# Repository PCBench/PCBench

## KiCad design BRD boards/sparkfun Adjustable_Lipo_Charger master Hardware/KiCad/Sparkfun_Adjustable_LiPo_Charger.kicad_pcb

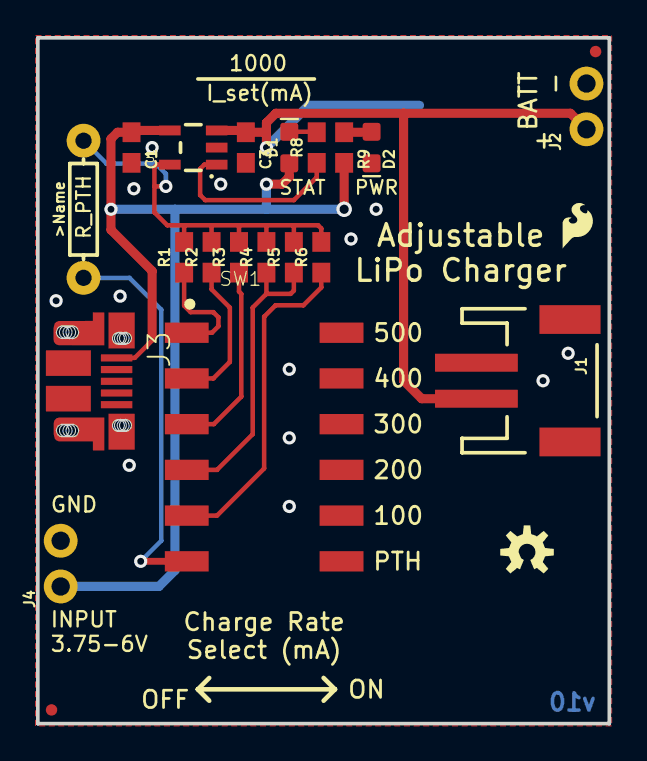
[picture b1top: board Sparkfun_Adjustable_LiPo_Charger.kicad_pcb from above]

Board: 2 copper layers, 31.8 x 38.1 mm, 28 parts (0 on the bottom side), 14 nets.

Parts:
BT1: BATTERY-24.5MM_SMD; BATTCON_24.5MM_SMD
C1, C3: 4.7uF; 0603
D1: BLUE; LED-0603
D2: RED; LED-0603
FD1, FD2, FD3, FD4: FIDUCIALUFIDUCIAL; FIDUCIAL-MICRO
FRAME1: FRAME-LETTER; CREATIVE_COMMONS
J1: JST_2MM_MALE; JST-2-SMD
J2, J4: CONN_021X02_NO_SILK; 1X02_NO_SILK
J3: USB_MICRO-B_HALF_PTH; USB-MICROB-PTH
LOGO1: SFE_LOGO_FLAME.1_INCH; SFE_LOGO_FLAME_.1
LOGO2: OSHW-LOGOS; OSHW-LOGO-S
R1: 2.0k; 0603
R2: 2.49k; 0603
R3: 3.3k; 0603
R4, R5, R6: 10k; 0603
R7: PTH; AXIAL-0.3
R8: 330; 0603
R9: 470; 0603
SW1: DIP-06; DIPSWITCH-06-SMD
U1: MCP73831; SOT23-5
U$1: SFE_LOGO_NAME_FLAME_.1

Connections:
/PROG: R1.2, R2.2, R3.2, R4.2, R5.2, R6.2, R7.P$2, U1.5
GND: BT1.2, C1.2, C3.2, D2.C, J1.1, J2.2, J3.GND, J4.2, SW1.7, SW1.8, SW1.9, SW1.10, SW1.11, SW1.12, U1.2
unnamed: D1.C, R8.2
unnamed: D2.A, R9.1
unnamed: J3.P$1, J3.P$2, J3.P$3, J3.P$4, J3.P$6, J3.P$8, J3.P$10, J3.P$12, J3.SHEILD2, J3.SHIELD, J3.SHIELD3, J3.SHIELD4
unnamed: R1.1, SW1.1
unnamed: R2.1, SW1.2
unnamed: R3.1, SW1.3
unnamed: R4.1, R5.1, SW1.4
unnamed: R6.1, SW1.5
unnamed: R7.P$1, SW1.6
unnamed: R8.1, U1.1
VCC: C1.1, D1.A, J3.VBUS, J4.1, R9.2, U1.4
V_BATT: BT1.3, C3.1, J1.2, J2.1, U1.3

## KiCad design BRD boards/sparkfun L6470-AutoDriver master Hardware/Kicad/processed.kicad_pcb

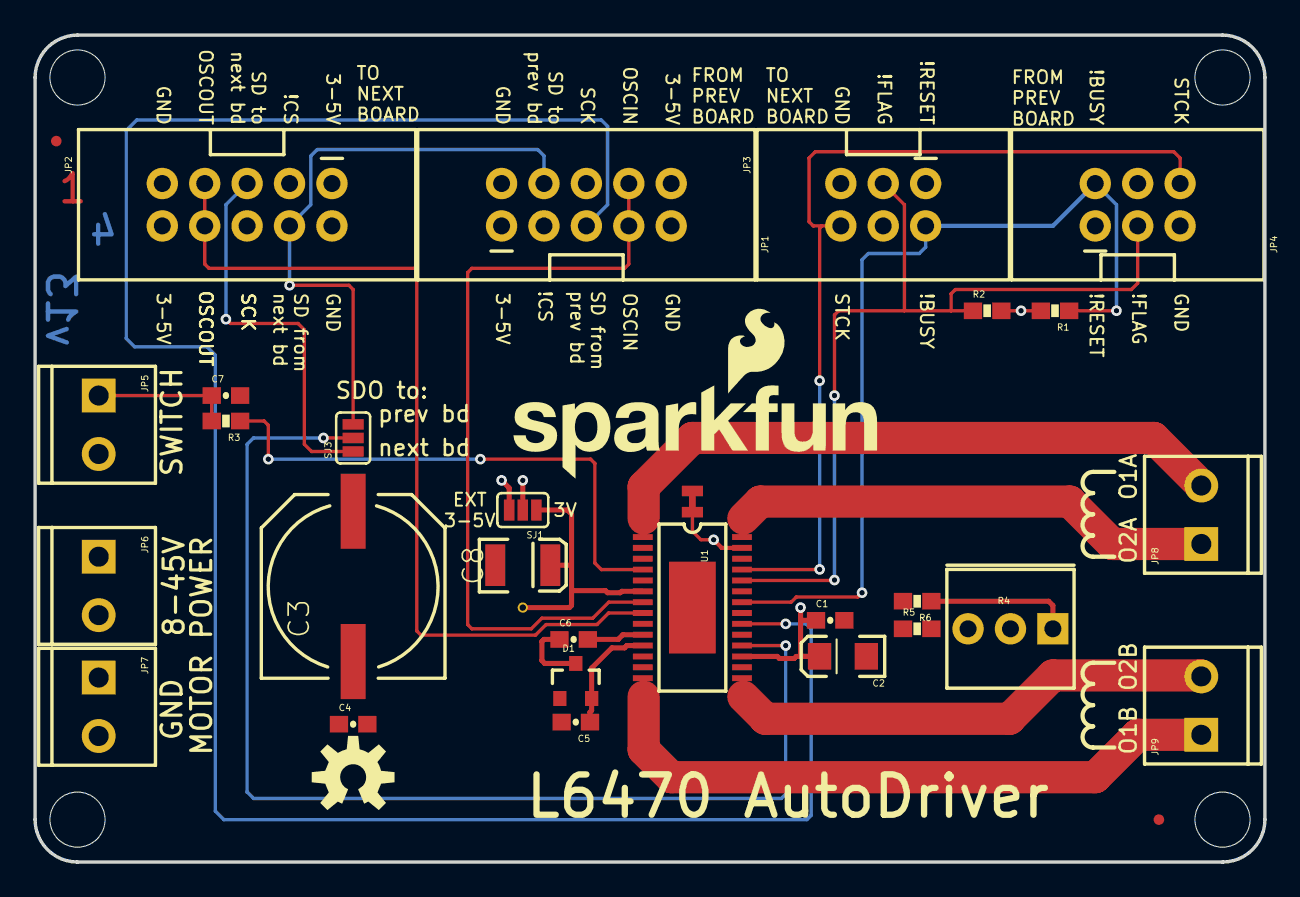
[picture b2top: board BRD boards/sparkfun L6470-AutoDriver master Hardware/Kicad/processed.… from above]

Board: 4 copper layers, 73.7 x 49.5 mm, 39 parts (0 on the bottom side), 23 nets.

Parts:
C1: 0.1uF; 0603-CAP
C2: 10uF; EIA3216
C3: 100uF; NIC_10X10.5_CAP
C4, C5: 0.22uF; 0603-CAP
C6, C7: 10nF; 0603-CAP
C8: 47uF; EIA3528
D1: BAV99; SOT23-3
FID1, FID2: FIDUCIALUFIDUCIAL; MICRO-FIDUCIAL
FRAME1: FRAME-LETTER; CREATIVE_COMMONS
JP1, JP2: M05X2SHD; 2X5-SHROUDED
JP3, JP4: M03X2SHROUD; 2X3-SHROUDED
JP5, JP6, JP7, JP8, JP9: M023.5MM; SCREWTERMINAL-3.5MM-2
LOGO1: OSHW-LOGOM; OSHW-LOGO-M
LOGO2: SFE_LOGO_NAME_FLAME.2_INCH; SFE_LOGO_NAME_FLAME_.2
R1, R2: 10k; 0603-RES
R3: 100; 0603-RES
R4: 200k; 3362U
R5: 8.2k; 0603-RES
R6: 33k; 0603-RES
SJ1, SJ3: JUMPER-PAD-3-2OF3_NC_BY_PASTE; PAD-JUMPER-3-2OF3_NC_BY_PASTE_YES_SILK_FULL_BOX
SJ2: 2PT_GND_TIE
STANDOFF1, STANDOFF2, STANDOFF3, STANDOFF4: STAND-OFF
TP1: TEST-POINTTP_15TH_THRU; TP_15TH
U1: L6470; HTSSOP28
U$4: FOUR_LAYER_WARNING

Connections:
3.3V: C8.A, SJ1.1, TP1.P$1, U1.6
5V: JP1.1, JP1.10, JP2.1, JP2.10, SJ1.3
/BUSYN: JP3.2, JP4.2, R1.1, U1.22
/D_RETURN: JP1.4, JP2.4, SJ3.3
/FLAGN: JP3.3, JP4.3, R2.1, U1.24
/OSCIN: JP1.7, JP1.8, U1.7
/OSCOUT: JP2.7, JP2.8, U1.8
/OUT1A: JP8.2, U1.1
/OUT1B: JP9.1, U1.14
/OUT2A: JP8.1, U1.28
/OUT2B: JP9.2, U1.15
/PGND: SJ2.P$2, U1.27
/SDI: JP1.5, U1.20
/SDO: SJ3.2, U1.18
/SDO_DOWNSTREAM: JP2.5, SJ3.1
/STCK: JP3.6, JP4.6, U1.25
/VLOGIC: C1.1, C2.A, R1.2, R2.2, SJ1.2, U1.17
unnamed: C5.1, D1.2, U1.11
unnamed: C6.1, D1.3
unnamed: C6.2, U1.10
unnamed: C7.1, JP5.1, R3.2
unnamed: R3.1, U1.4
unnamed: R4.P$1, R6.1

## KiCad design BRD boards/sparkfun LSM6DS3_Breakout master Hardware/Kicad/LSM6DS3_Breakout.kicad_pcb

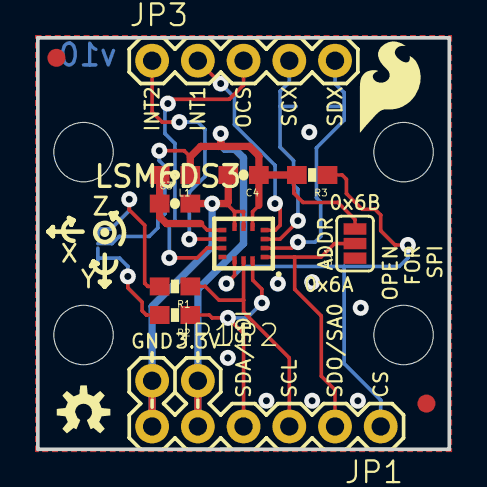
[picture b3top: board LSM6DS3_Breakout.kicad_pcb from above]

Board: 2 copper layers, 22.9 x 22.9 mm, 25 parts (0 on the bottom side), 14 nets.

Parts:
C3, C4: 0.1uF; 0603-CAP
FID1, FID2: FIDUCIAL1X2; FIDUCIAL-1X2
FRAME1: CREATIVE_COMMONS
JP1: IO; 1X06_NO_SILK_YES_STOP
JP2: 3.3V; 1X01_NO_SILK
JP3: IO; 1X05
JP11: GND; 1X01_NO_SILK
L1: RES-07859; 0603
LOGO1: SFE_LOGO_FLAME.2_INCH; SFE_LOGO_FLAME_.2
LOGO2: OSHW-LOGOS; OSHW-LOGO-S
LOGO3: SFE_LOGO_NAME_FLAME.1_INCH; SFE_LOGO_NAME_FLAME_.1
R1, R2: 4.7K; 0603-RES
R3: 10K; 0603-RES
SJ1: PAD-JUMPER-3-2OF3_NC_BY_PASTE_YES_SILK_FULL_BOX
SJ2: S_MODE; PAD-JUMPER-3-3OF3_NC_BY_TRACE_YES_SILK_FULL_BOX
SJ3, SJ4: JUMPER-PAD-2-NC_BY_TRACE; PAD-JUMPER-2-NC_BY_TRACE_YES_SILK
STANDOFF1, STANDOFF2, STANDOFF3, STANDOFF4: STAND-OFF
U2: LSM6DS3; LGA14L_DOT_INDICATOR

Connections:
3.3V: C4.1, JP1.5, JP2.1, L1.1, R3.2, SJ1.3, SJ2.2, U2.5
CS: JP1.1, R3.1, U2.12
GND: C3.2, C4.2, JP1.6, JP11.1, SJ1.1, SJ3.1, SJ4.1, U2.6, U2.7
INT1: JP3.2, U2.4
INT2: JP3.1, U2.9
unnamed: R1.2, SJ2.1
unnamed: R2.2, SJ2.3
OCS: JP3.3, U2.10
SCL: JP1.3, R1.1, U2.13
SCX: JP3.4, SJ4.2, U2.3
SDA: JP1.4, R2.1, U2.14
SDO/SA0: JP1.2, SJ1.2, U2.1
SDX: JP3.5, SJ3.2, U2.2
VDD: C3.1, L1.2, U2.8

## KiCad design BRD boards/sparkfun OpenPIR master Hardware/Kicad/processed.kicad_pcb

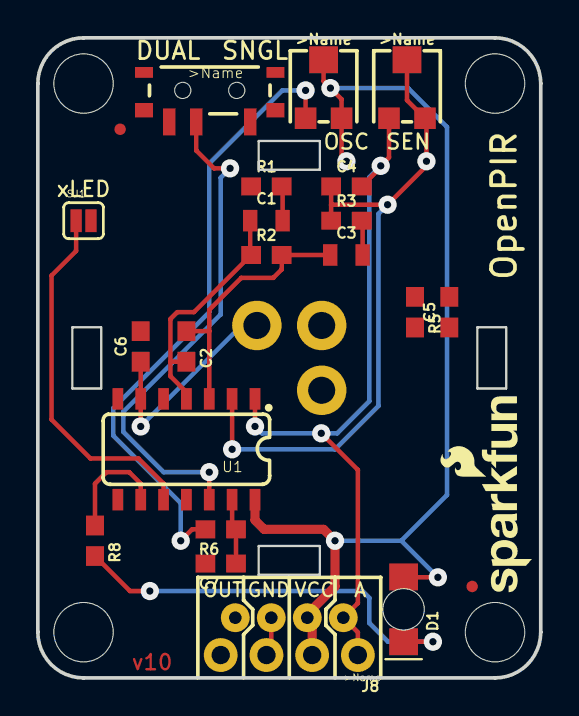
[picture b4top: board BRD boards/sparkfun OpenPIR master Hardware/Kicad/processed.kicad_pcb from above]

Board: 2 copper layers, 27.9 x 35.6 mm, 35 parts (0 on the bottom side), 15 nets.

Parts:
C1, C3: 22uF; 0805
C2, C4: 10nF; 0603
C5, C6, C7: 0.1uF; 0603
D1: Green; LED-1206-BOTTOM
FD1, FD2: FIDUCIALUFIDUCIAL; MICRO-FIDUCIAL
FRAME1: FRAME-LETTER; CREATIVE_COMMONS
H1, H2, H3, H4: STAND-OFF
J2: CONN_04JST-PTH-VERT-NS; JST-4-PTH-VERT-NS
J8: CONN_04NO_SILK_ALL_ROUND; 1X04_NO_SILK_ALL_ROUND
LOGO1: SFE_LOGO_NAME_FLAME.1_INCH; SFE_LOGO_NAME_FLAME_.1
LOGO3: SFE_LOGO_NAME.1_INCH; SFE_LOGO_NAME_.1
LOGO4: OSHW-LOGOS; OSHW-LOGO-S
R1, R3: 10k; 0603
R2: 560k; 0603
R4, R7: 1M; TRIMPOT-TC33X
R5: 43k; 0603
R6: 51k; 0603
R8: 1k; 0603
S1: SWITCH-SPDT-SMD-A; SWITCH-SPST-SMD-A
SJ1: LED-EN; SJ_2S
TP1, TP2: TEST-POINT3X5; PAD.03X.05
U1: NCS36000; SO14
U2: PIR
U$1: CWM 0.5 GI V1; LENS-CWM-0.5-GI-V1

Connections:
/A_OUT: C4.2, J2.1, J8.1, R4.1, U1.1
/LED: R8.1, U1.9
/MODE: S1.2, U1.12
/~LED_EN~: SJ1.1, U1.10
GND: J2.3, J8.3
unnamed: C1.1, C2.2, R2.1, U1.4
unnamed: C1.2, R1.2
unnamed: C2.1, C3.1, R2.2, U1.3
unnamed: C3.2, R3.2
unnamed: C4.1, R3.1, R4.2, R4.3, U1.2
unnamed: C6.1, U1.6, U2.D
unnamed: C7.1, R6.1, U1.13
unnamed: D1.C, R8.2
unnamed: R6.2, R7.1
VCC: D1.A, J2.2, J8.2, R7.2, R7.3, U1.14

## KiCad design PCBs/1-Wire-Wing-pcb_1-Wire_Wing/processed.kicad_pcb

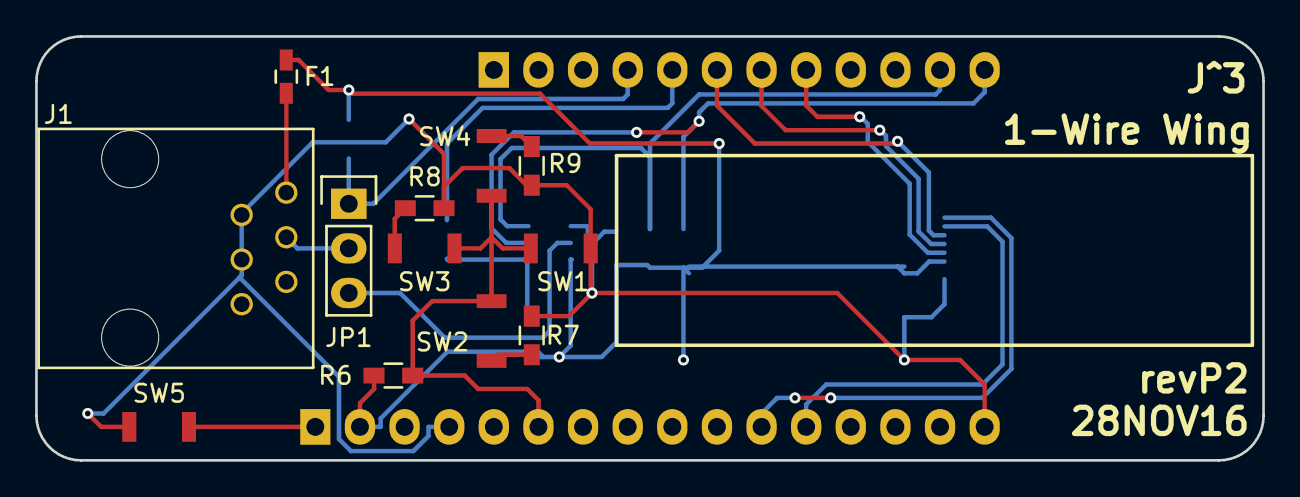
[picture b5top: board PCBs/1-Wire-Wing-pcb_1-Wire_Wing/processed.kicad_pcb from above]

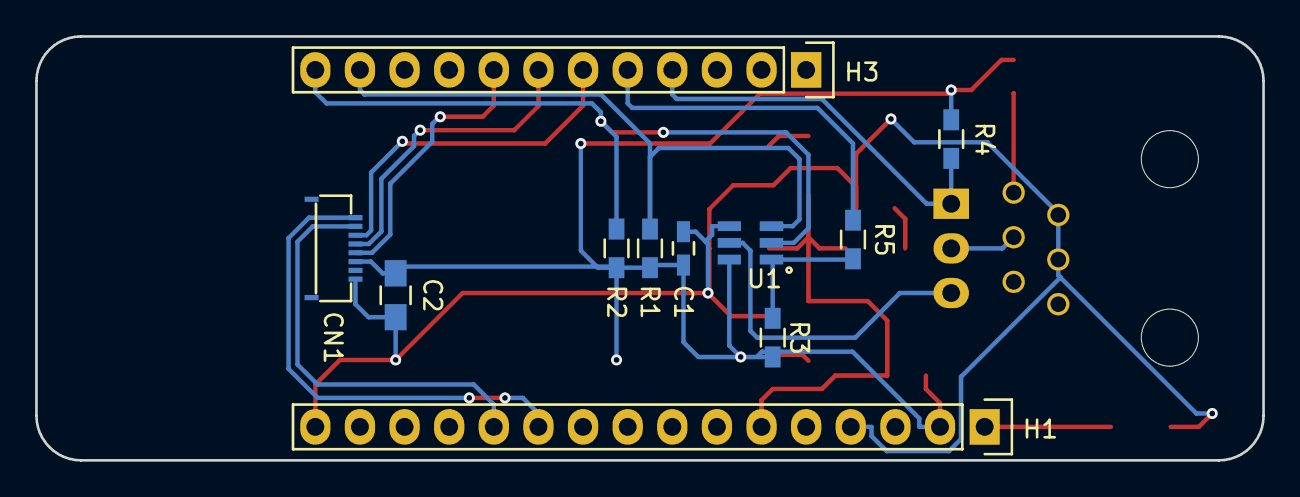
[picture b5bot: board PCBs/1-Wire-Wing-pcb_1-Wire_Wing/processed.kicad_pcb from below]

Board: 2 copper layers, 69.9 x 24.1 mm, 23 parts (11 on the bottom side), 20 nets.

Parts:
C1: 0.1uF; C_0603_HandSoldering
C2: 2uF; C_0805_HandSoldering
CN1: CONN_01X08; HIROSE_FH19C-8S-0.5SH(05)
F1: FUSE; C_0603_HandSoldering
H1: CONN_01X16; Pin_Header_Straight_1x16
H3: CONN_01X12; Pin_Header_Straight_1x12
J1: RJ11; TE_6P6C_5555165-1
JP1: CONN_01X03; Pin_Header_Straight_1x03
R1, R2, R7: 3.3K; R_0603_HandSoldering
R3: 2.2K; R_0603_HandSoldering
R4: 1K; R_0603_HandSoldering
R5: DNI; R_0603_HandSoldering
R6, R8: 10K; R_0603_HandSoldering
R9: 33K; R_0603_HandSoldering
SW1, SW2, SW3, SW4, SW5: SW_PUSH_SMALL_H; OMRON_B3U-1000P
U1: DS2484R+; SOT95P280X125-6N

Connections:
+3V3: C1.1, C2.1, CN1.6, F1.1, H1.2, R1.1, R2.1, R3.1, R4.1, R6.1, U1.6
/1-Wire: J1.3, JP1.2
/CS: CN1.3, H3.6
/DISP: CN1.5, H3.8
/EXTCOMIN: CN1.4, H3.7
/MOSI: CN1.2, H1.12
/OWM: H3.4, JP1.1, R4.2
/SCL: H3.11, R1.2, U1.3
/SCLK: CN1.1, H1.11
/SDA: H3.12, R2.2, U1.2
/~RESET: H1.1, SW5.1
/~SLPZ: H3.5, R5.2
GND: C1.2, C2.2, CN1.8, H1.4, H1.16, J1.2, J1.4, R7.2, R8.2, R9.2, SW1.1, SW5.2, U1.4
unnamed: F1.2, J1.1
unnamed: H1.6, R6.2, SW1.2, SW2.2, SW3.2, SW4.2
unnamed: JP1.3, U1.5
unnamed: R3.2, R5.1, U1.1
unnamed: R7.1, SW2.1
unnamed: R8.1, SW3.1
unnamed: R9.1, SW4.1

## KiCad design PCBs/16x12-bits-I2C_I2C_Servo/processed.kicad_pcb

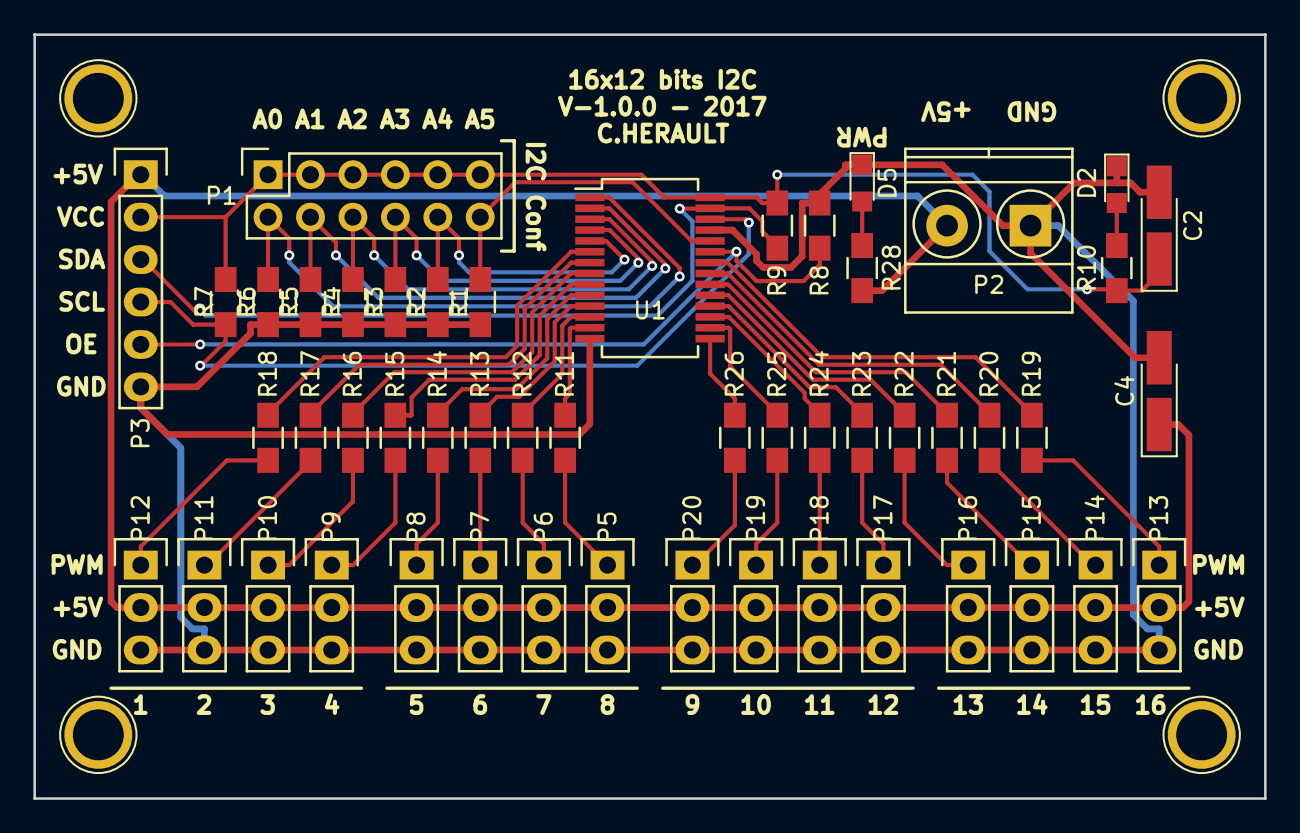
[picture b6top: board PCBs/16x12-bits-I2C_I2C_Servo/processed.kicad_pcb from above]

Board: 2 copper layers, 73.7 x 45.7 mm, 51 parts (0 on the bottom side), 46 nets.

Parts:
C2, C4: 10uF; CP_Tantalum_Case-S_EIA-3216-12_Hand
D2, D5: LED_Small; LED_0805
P1: CONN_02X06; Socket_Strip_Straight_2x06
P2: CONN_01X02; TerminalBlock_Pheonix_MKDS1.5-2pol
P3: CONN_01X06; Socket_Strip_Straight_1x06
P5, P6, P7, P8, P9, P10, P11, P12, P13, P14, P15, P16, P17, P18, P19, P20: CONN_01X03; Socket_Strip_Straight_1x03
R1, R2, R3, R4, R5, R6, R7, R8, R9: 10K; R_0805_HandSoldering
R10, R28: 470; R_0805_HandSoldering
R11, R12, R13, R14, R15, R16, R17, R18, R19, R20, R21, R22, R23, R24, R25, R26: 220; R_0805_HandSoldering
U1: PCA9685; SSOP-28_5.3x10.2mm_Pitch0.65mm

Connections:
+5V: C4.1, P2.2, P3.1, P5.2, P6.2, P7.2, P8.2, P9.2, P10.2, P11.2, P12.2, P13.2, P14.2, P15.2, P16.2, P17.2, P18.2, P19.2, P20.2, R28.2
GND: C2.2, C4.2, D2.1, D5.1, P2.1, P3.6, P5.3, P6.3, P7.3, P8.3, P9.3, P10.3, P11.3, P12.3, P13.3, P14.3, P15.3, P16.3, P17.3, P18.3, P19.3, P20.3, R1.2, R2.2, R3.2, R4.2, R5.2, R6.2, R8.2, U1.14, U1.25
unnamed: D2.2, R10.1
unnamed: D5.2, R28.1
unnamed: P1.2, R6.1, U1.1
unnamed: P1.4, R5.1, U1.2
unnamed: P1.6, R4.1, U1.3
unnamed: P1.8, R3.1, U1.4
unnamed: P1.10, R2.1, U1.5
unnamed: P1.12, R1.1, U1.24
unnamed: P5.1, R11.1
unnamed: P6.1, R12.1
unnamed: P7.1, R13.1
unnamed: P8.1, R14.1
unnamed: P9.1, R15.1
unnamed: P10.1, R16.1
unnamed: P11.1, R17.1
unnamed: P12.1, R18.1
unnamed: P13.1, R19.1
unnamed: P14.1, R20.1
unnamed: P15.1, R21.1
unnamed: P16.1, R22.1
unnamed: P17.1, R23.1
unnamed: P18.1, R24.1
unnamed: P19.1, R25.1
unnamed: P20.1, R26.1
OE: P3.5, R8.1, U1.23
PWM0: R18.2, U1.6
PWM1: R17.2, U1.7
PWM2: R16.2, U1.8
PWM3: R15.2, U1.9
PWM4: R14.2, U1.10
PWM5: R13.2, U1.11
PWM6: R12.2, U1.12
PWM7: R11.2, U1.13
PWM8: R26.2, U1.15
PWM9: R25.2, U1.16
PWM10: R24.2, U1.17
PWM11: R23.2, U1.18
PWM12: R22.2, U1.19
PWM13: R21.2, U1.20
PWM14: R20.2, U1.21
PWM15: R19.2, U1.22
SCL: P3.4, R7.2, U1.26
SDA: P3.3, R9.2, U1.27
VCC: C2.1, P1.1, P1.3, P1.5, P1.7, P1.9, P1.11, P3.2, R7.1, R9.1, R10.2, U1.28

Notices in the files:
parts and their libraries:
https://creativecommons.org/licenses/by-sa/4.0
Released under the Creative Commons Attribution Share-Alike 4.0 License
